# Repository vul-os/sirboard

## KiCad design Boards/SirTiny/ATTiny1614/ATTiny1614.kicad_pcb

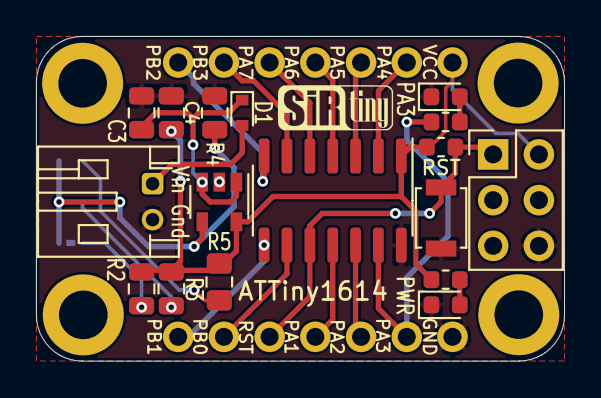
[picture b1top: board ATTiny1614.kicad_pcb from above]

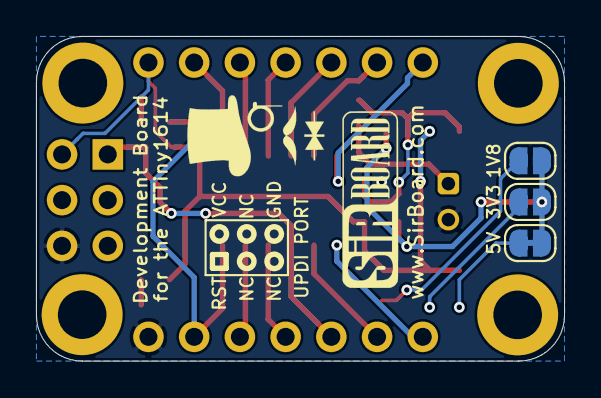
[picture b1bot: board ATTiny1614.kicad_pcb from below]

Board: 2 copper layers, 29.3 x 18.0 mm, 22 parts (5 on the bottom side), 22 nets.

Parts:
1V8, 3V3: SolderJumper_2_Open; SolderJumper-2_P1.3mm_Open_RoundedPad1.0x1.5mm
5V: SolderJumper_2_Bridged; SolderJumper-2_P1.3mm_Bridged_RoundedPad1.0x1.5mm
ATTiny1614: ATtiny1614-SS; SOIC-14_3.9x8.7mm_P1.27mm
C3: 2.2uF; C_0805_2012Metric
C4: 1uF; C_0805_2012Metric
D1: 1N4148WT; D_SOD-523
J1, J3: Conn_01x07; PinHeader_1x07_P2.54mm_Vertical
J4: ISP6; PinHeader_2x03_P2.54mm_Vertical
PA3: SFH460; LED_0603_1608Metric
PWR: SFH460; LED_0603_1608Metric
R1: 10k; R_0603_1608Metric
R2: 33K; R_0805_2012Metric
R3: 60K; R_0805_2012Metric
R4: 100K; R_0805_2012Metric
R5: 220K; R_0805_2012Metric_Pad1.15x1.40mm_HandSolder
R6, R7: 1k; R_0603_1608Metric
RST: RST; SW_SPST_B3U-1000P
U1: AP2204K-ADJ; SOT-23-5
Vin Gnd: Conn_01x02; JST_PH_S2B-PH-K_1x02_P2.00mm_Horizontal

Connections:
GND: ATTiny1614.14, C3.2, C4.2, J3.1, J4.6, PA3.1, PWR.1, R4.2, RST.2, U1.2, Vin Gnd.2
unnamed: 1V8.1, 3V3.1, 5V.2, R4.1, U1.4
unnamed: 1V8.2, R5.2
unnamed: 3V3.2, R3.2
unnamed: 5V.1, R2.2
unnamed: C3.1, D1.1, U1.1, U1.3
unnamed: PWR.2, R7.2
unnamed: PA3.2, R6.2
PA1: ATTiny1614.11, J3.4
PA2: ATTiny1614.12, J3.3
PA3: ATTiny1614.13, J3.2, R6.1
PA4: ATTiny1614.2, J1.2
PA5: ATTiny1614.3, J1.3
PA6: ATTiny1614.4, J1.4
PA7: ATTiny1614.5, J1.5
PB0: ATTiny1614.9, J3.6
PB1: ATTiny1614.8, J3.7
PB2: ATTiny1614.7, J1.7
PB3: ATTiny1614.6, J1.6
RST: ATTiny1614.10, J3.5, J4.1, R1.1, RST.1
VCC: ATTiny1614.1, C4.1, J1.1, J4.2, R1.2, R2.1, R3.1, R5.1, R7.1, U1.5
VIN: D1.2, Vin Gnd.1

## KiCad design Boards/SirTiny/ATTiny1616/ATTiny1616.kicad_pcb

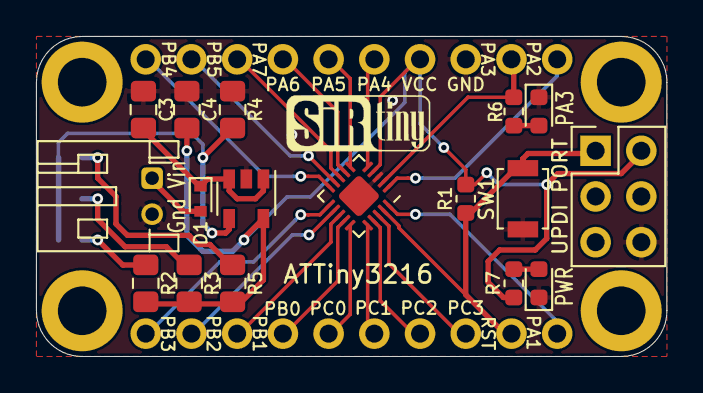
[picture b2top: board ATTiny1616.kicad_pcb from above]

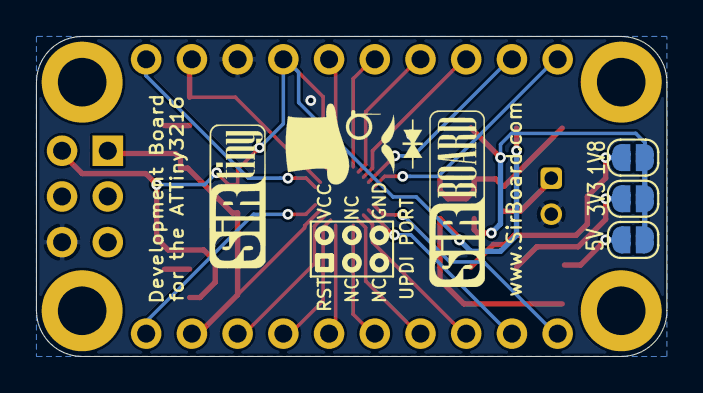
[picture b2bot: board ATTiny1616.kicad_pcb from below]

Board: 2 copper layers, 35.0 x 17.8 mm, 22 parts (5 on the bottom side), 28 nets.

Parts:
1V8, 3V3, 5V: SolderJumper_2_Open; SolderJumper-2_P1.3mm_Open_RoundedPad1.0x1.5mm
C3: 2.2uF; C_0805_2012Metric_Pad1.15x1.40mm_HandSolder
C4: 1uF; C_0805_2012Metric_Pad1.15x1.40mm_HandSolder
D1: 1N4148WT; D_SOD-523
Gnd Vin: Conn_01x02; JST_PH_S2B-PH-K_1x02_P2.00mm_Horizontal
J1, J3: Conn_01x10; PinHeader_1x10_P2.54mm_Vertical
PA3: SFH460; LED_0603_1608Metric
PWR: SFH460; LED_0603_1608Metric
R1: 10k; R_0603_1608Metric
R2: 33K; R_0805_2012Metric_Pad1.15x1.40mm_HandSolder
R3: 60K; R_0805_2012Metric_Pad1.15x1.40mm_HandSolder
R4: 100K; R_0805_2012Metric_Pad1.15x1.40mm_HandSolder
R5: 220K; R_0805_2012Metric_Pad1.15x1.40mm_HandSolder
R6, R7: 1k; R_0603_1608Metric
SW1: RST; SW_SPST_B3U-1000P
U1: AP2204K-ADJ; SOT-23-5
U2: ATtiny3216-M; UQFN-20-1EP_3x3mm_P0.4mm_EP1.85x1.85mm
UPDI PORT: ISP6; PinHeader_2x03_P2.54mm_Vertical

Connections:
GND: C3.2, C4.2, Gnd Vin.2, J1.3, PA3.1, PWR.1, R4.2, SW1.2, U1.2, U2.3, U2.21, UPDI PORT.6
unnamed: 1V8.1, 3V3.1, 5V.1, R4.1, U1.4
unnamed: 1V8.2, R5.2
unnamed: 3V3.2, R3.2
unnamed: 5V.2, R2.2
unnamed: C3.1, D1.1, U1.1, U1.3
unnamed: PWR.2, R7.2
unnamed: PA3.2, R6.2
PA1: J3.1, U2.20
PA2: J1.1, U2.1
PA3: J1.2, R6.1, U2.2
PA4: J1.5, U2.5
PA5: J1.6, U2.6
PA6: J1.7, U2.7
PA7: J1.8, U2.8
PB0: J3.7, U2.14
PB1: J3.8, U2.13
PB2: J3.9, U2.12
PB3: J3.10, U2.11
PB4: J1.10, U2.10
PB5: J1.9, U2.9
PC0: J3.6, U2.15
PC1: J3.5, U2.16
PC2: J3.4, U2.17
PC3: J3.3, U2.18
RST: J3.2, R1.1, SW1.1, U2.19, UPDI PORT.1
VCC: C4.1, J1.4, R1.2, R2.1, R3.1, R5.1, R7.1, U1.5, U2.4, UPDI PORT.2
VIN: D1.2, Gnd Vin.1

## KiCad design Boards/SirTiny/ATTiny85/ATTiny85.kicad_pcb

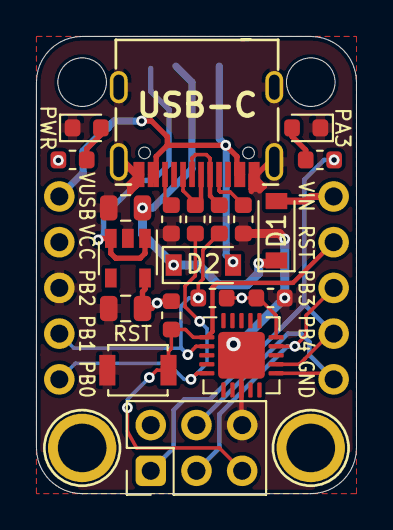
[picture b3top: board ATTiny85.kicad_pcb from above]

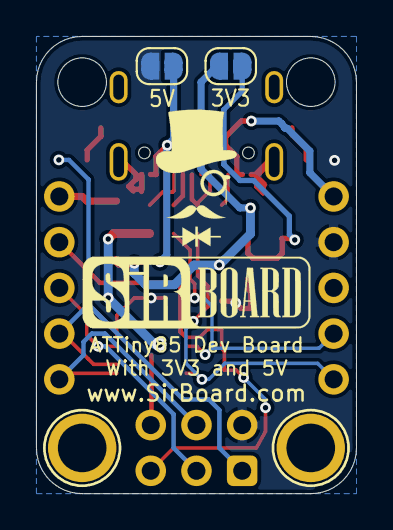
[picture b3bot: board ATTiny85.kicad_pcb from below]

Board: 2 copper layers, 17.8 x 25.4 mm, 28 parts (4 on the bottom side), 18 nets.

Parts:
3V3, 5V: SolderJumper_2_Open; SolderJumper-2_P1.3mm_Open_RoundedPad1.0x1.5mm
C1, C2: 10uF; C_0805_2012Metric
C3: 100nF; C_0603_1608Metric
D1, D2: MBR120; D_SOD-123
H1, H4: MountingHole; MountingHole_2.7mm_M2.5
H2, H3: MountingHole; MountingHole_M2.5_SirBoard
J2, J3: Conn_01x05; PinHeader_1x05_P2.54mm_Vertical
J4: ISP6; PinHeader_2x03_P2.54mm_Vertical
PA3: RED; LED_0603_1608Metric
PWR: RED; LED_0603_1608Metric
R1, R2: 5k1; R_0603_1608Metric
R3, R4: 68e; R_0603_1608Metric
R5: 10K; R_0603_1608Metric
R6: 1k5; R_0603_1608Metric
R7, R8: 1K; R_0603_1608Metric
RST: SW_SPST; SW_SPST_B3U-1000P
U1: ATtiny85-20MU; QFN-20-1EP_4x4mm_P0.5mm_EP2.6x2.6mm
U2: SPX3819M5-L-3-3; SOT-23-5
USB-C: USB_C_Receptacle_USB2.0; USB_C

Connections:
GND: C1.2, C2.2, C3.2, J2.3, J4.6, PA3.1, PWR.1, R1.2, R2.2, RST.2, U1.8, U1.21, U2.2, USB-C.A1, USB-C.A12, USB-C.B1, USB-C.B12, USB-C.S1
unnamed: 3V3.1, C1.1, D1.1, D2.1
unnamed: 3V3.2, U2.1, U2.3
unnamed: PA3.2, R7.1
unnamed: PWR.2, R8.1
unnamed: R2.1, USB-C.A5
unnamed: R4.1, USB-C.A6, USB-C.B6
unnamed: R3.1, USB-C.A7, USB-C.B7
unnamed: R1.1, USB-C.B5
PB0: J3.5, J4.4, U1.11
PB1: J3.4, J4.1, R7.2, U1.12
PB2: J3.3, J4.3, U1.14
PB3: J2.4, R3.2, R6.1, U1.2
PB4: J2.5, R4.2, U1.5
RST: J3.2, J4.5, R5.1, RST.1, U1.1
VCC: 5V.2, C2.1, C3.1, J2.2, J4.2, R5.2, R6.2, R8.2, U1.15, U2.5
VIN: D1.2, J3.1
VUSB: 5V.1, D2.2, J2.1, USB-C.A4, USB-C.A9, USB-C.B4, USB-C.B9

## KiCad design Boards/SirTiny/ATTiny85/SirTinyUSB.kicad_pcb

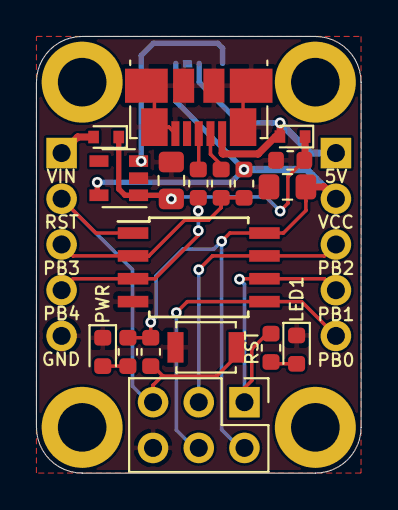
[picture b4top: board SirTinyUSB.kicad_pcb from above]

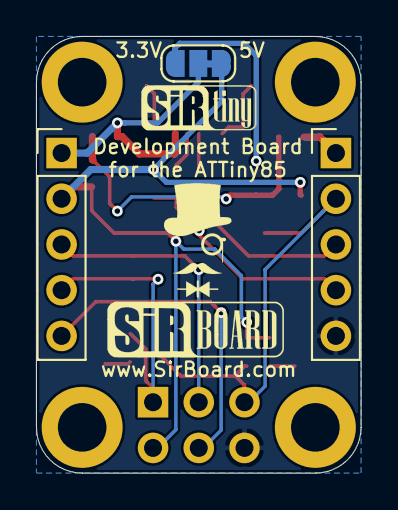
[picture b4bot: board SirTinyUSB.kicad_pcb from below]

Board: 2 copper layers, 18.0 x 24.3 mm, 21 parts (3 on the bottom side), 16 nets.

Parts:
3.3V       5V: SolderJumper_3_Bridged12; SolderJumper-3_P1.3mm_Bridged12_RoundedPad1.0x1.5mm
C1: 1uF; C_0603_1608Metric
C3, C4: 10uF; C_0805_2012Metric_Pad1.15x1.40mm_HandSolder
D1, D2: 1N4148WT; D_SOD-523
J2, J3: Conn_01x05; PinHeader_1x05_P2.54mm_Vertical
J4: ISP6; PinHeader_2x03_P2.54mm_Vertical
LED1: SFH460; LED_0603_1608Metric
PS1: 1; SOT-23-5
PWR: SFH460; LED_0603_1608Metric
R4, R7: 1k; R_0603_1608Metric
R5: 33k; R_0603_1608Metric
R6, R9: 68e; R_0603_1608Metric
R8: 1k5; R_0603_1608Metric
RST: SW_SPST; SW_SPST_B3U-1000P
U1: ATtiny85-20SU; SOIJ-8_5.3x5.3mm_P1.27mm
USB1: USB_B_Micro; USB_Micro-B_Molex_47346-0001

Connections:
5V: 3.3V 5V.2, D2.2, J2.1, USB1.1
GND: C1.2, C3.2, C4.2, J3.5, J4.6, LED1.1, PS1.2, PWR.1, RST.2, U1.4, USB1.5, USB1.6
unnamed: C1.1, C3.1, D1.1, D2.1, PS1.1
unnamed: 3.3V 5V.3, PS1.3
unnamed: LED1.2, R7.2
unnamed: PWR.2, R4.2
unnamed: R6.1, USB1.3
unnamed: R9.2, USB1.2
PB0: J2.5, J4.4, U1.5
PB1: J2.4, J4.1, R7.1, U1.6
PB2: J2.3, J4.3, U1.7
PB3: J3.3, R8.1, R9.1, U1.2
PB4: J3.4, R6.2, U1.3
RST: J3.2, J4.5, R5.1, RST.1, U1.1
VCC: 3.3V 5V.1, C4.1, J2.2, J4.2, PS1.5, R4.1, R5.2, R8.2, U1.8
VIN: D1.2, J3.1

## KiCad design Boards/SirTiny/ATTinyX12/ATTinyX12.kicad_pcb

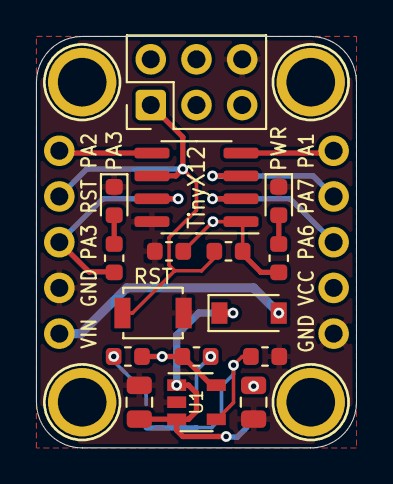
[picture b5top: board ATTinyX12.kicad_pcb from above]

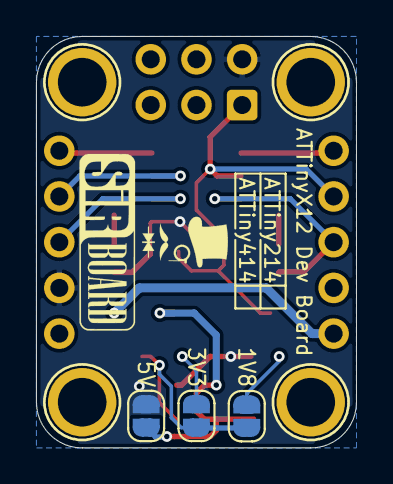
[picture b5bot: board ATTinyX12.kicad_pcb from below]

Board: 2 copper layers, 17.8 x 22.9 mm, 25 parts (5 on the bottom side), 15 nets.

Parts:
1V8, 3V3: SolderJumper_2_Open; SolderJumper-2_P1.3mm_Open_RoundedPad1.0x1.5mm
5V: SolderJumper_2_Bridged; SolderJumper-2_P1.3mm_Open_RoundedPad1.0x1.5mm
C1: 10uF; C_0805_2012Metric
C2: 2u2; C_0805_2012Metric
C3: 100nF; C_0603_1608Metric
D1: MBR120; D_SOD-123
H1, H2, H3, H4: MountingHole; MountingHole_M2.5_SirBoard
J1, J2: Conn_01x05; PinHeader_1x05_P2.54mm_Vertical
J4: UPDI; PinHeader_2x03_P2.54mm_Vertical
PA3: BLUE; LED_0603_1608Metric
PWR: RED; LED_0603_1608Metric
R1, R7: 1k; R_0603_1608Metric
R3: 39k; R_0603_1608Metric
R4: 12.4k; R_0603_1608Metric
R5: 18k; R_0603_1608Metric
R6: 10k; R_0603_1608Metric
RST: RST; SW_SPST_B3U-1000P
TinyX12: ATtiny412; SOIC-8_3.9x4.9mm_P1.27mm
U1: AP7365; SOT-23-5

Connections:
/1V8: 1V8.2, R5.2
/3V3: 3V3.2, R3.2
/ADJ: 1V8.1, 3V3.1, R4.1, U1.4
GND: C1.2, C2.2, C3.2, J1.1, J2.2, J4.6, PA3.1, PWR.1, R4.2, RST.2, TinyX12.8, U1.2
unnamed: 5V.1, C1.1, D1.1, U1.1, U1.3
unnamed: PWR.2, R1.2
unnamed: PA3.2, R7.2
PA1: J1.5, TinyX12.4
PA2: J2.5, TinyX12.5
PA3: J2.3, R7.1, TinyX12.7
PA6: J1.3, TinyX12.2
PA7: J1.4, TinyX12.3
RST: J2.4, J4.1, R6.2, RST.1, TinyX12.6
VCC: 5V.2, C2.1, C3.1, J1.2, J4.2, R1.1, R3.1, R5.1, R6.1, TinyX12.1, U1.5
VIN: D1.2, J2.1

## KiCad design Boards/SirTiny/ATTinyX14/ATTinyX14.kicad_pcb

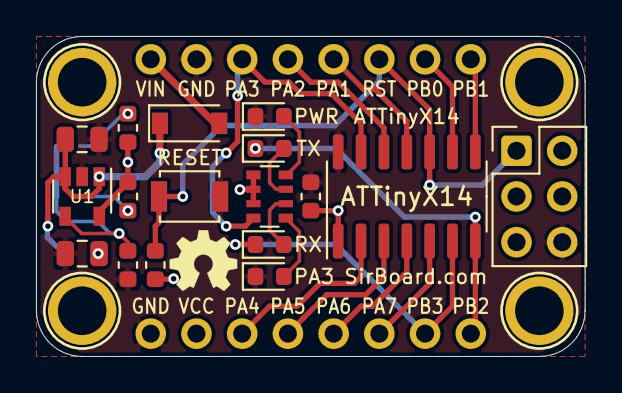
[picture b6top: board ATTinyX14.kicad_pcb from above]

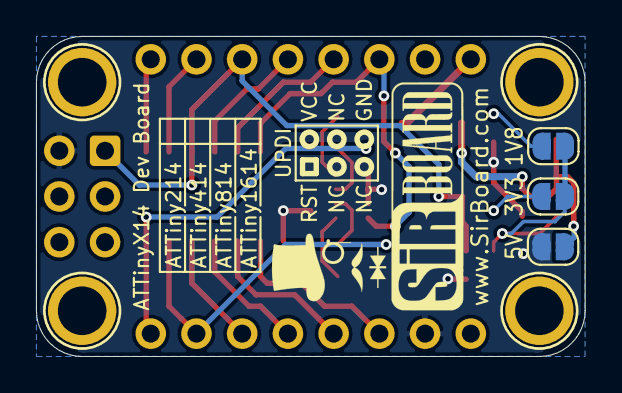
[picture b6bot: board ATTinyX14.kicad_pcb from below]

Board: 2 copper layers, 30.5 x 17.8 mm, 26 parts (5 on the bottom side), 23 nets.

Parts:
1V8, 3V3, 5V: SolderJumper_2_Open; SolderJumper-2_P1.3mm_Open_RoundedPad1.0x1.5mm
ATTinyX14: ATtiny1614-SS; SOIC-14_3.9x8.7mm_P1.27mm
C1: 10uF; C_0805_2012Metric
C2: 2u2; C_0805_2012Metric
C3: 100nF; C_0603_1608Metric
D1: MBR120; D_SOD-123
H1, H2, H3, H4: MountingHole; MountingHole_M2.5_SirBoard
J1, J2: Conn_01x08; PinHeader_1x08_P2.54mm_Vertical
J4: UPDI; PinHeader_2x03_P2.54mm_Vertical
PA3: BLUE; LED_0603_1608Metric
PWR: RED; LED_0603_1608Metric
R3: 39k; R_0603_1608Metric
R4: 12.4k; R_0603_1608Metric
R5: 18k; R_0603_1608Metric
R6: 10k; R_0603_1608Metric
RESET: RST; SW_SPST_B3U-1000P
RN1: 330E; R_Array_Convex_4x0603
RX: YEL; LED_0603_1608Metric
TX: YEL; LED_0603_1608Metric
U1: AP7365; SOT-23-5

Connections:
/1V8: 1V8.2, R5.2
/3V3: 3V3.2, R3.2
/ADJ: 1V8.1, 3V3.1, R4.1, U1.4
GND: ATTinyX14.14, C1.2, C2.2, C3.2, J1.1, J2.2, J4.6, PA3.1, PWR.1, R4.2, RESET.2, U1.2
unnamed: 5V.2, C1.1, D1.1, U1.1, U1.3
unnamed: PA3.2, RN1.1
unnamed: PWR.2, RN1.4
unnamed: RN1.2, RX.2
unnamed: RN1.3, TX.2
PA1: ATTinyX14.11, J2.5
PA2: ATTinyX14.12, J2.4
PA3: ATTinyX14.13, J2.3, RN1.8
PA4: ATTinyX14.2, J1.3
PA5: ATTinyX14.3, J1.4
PA6: ATTinyX14.4, J1.5
PA7: ATTinyX14.5, J1.6
PB0: ATTinyX14.9, J2.7
PB1: ATTinyX14.8, J2.8
RST: ATTinyX14.10, J2.6, J4.1, R6.2, RESET.1
RXD: ATTinyX14.6, J1.7, RX.1
TXD: ATTinyX14.7, J1.8, TX.1
VCC: 5V.1, ATTinyX14.1, C2.1, C3.1, J1.2, J4.2, R3.1, R5.1, R6.1, RN1.5, RN1.6, RN1.7, U1.5
VIN: D1.2, J2.1
